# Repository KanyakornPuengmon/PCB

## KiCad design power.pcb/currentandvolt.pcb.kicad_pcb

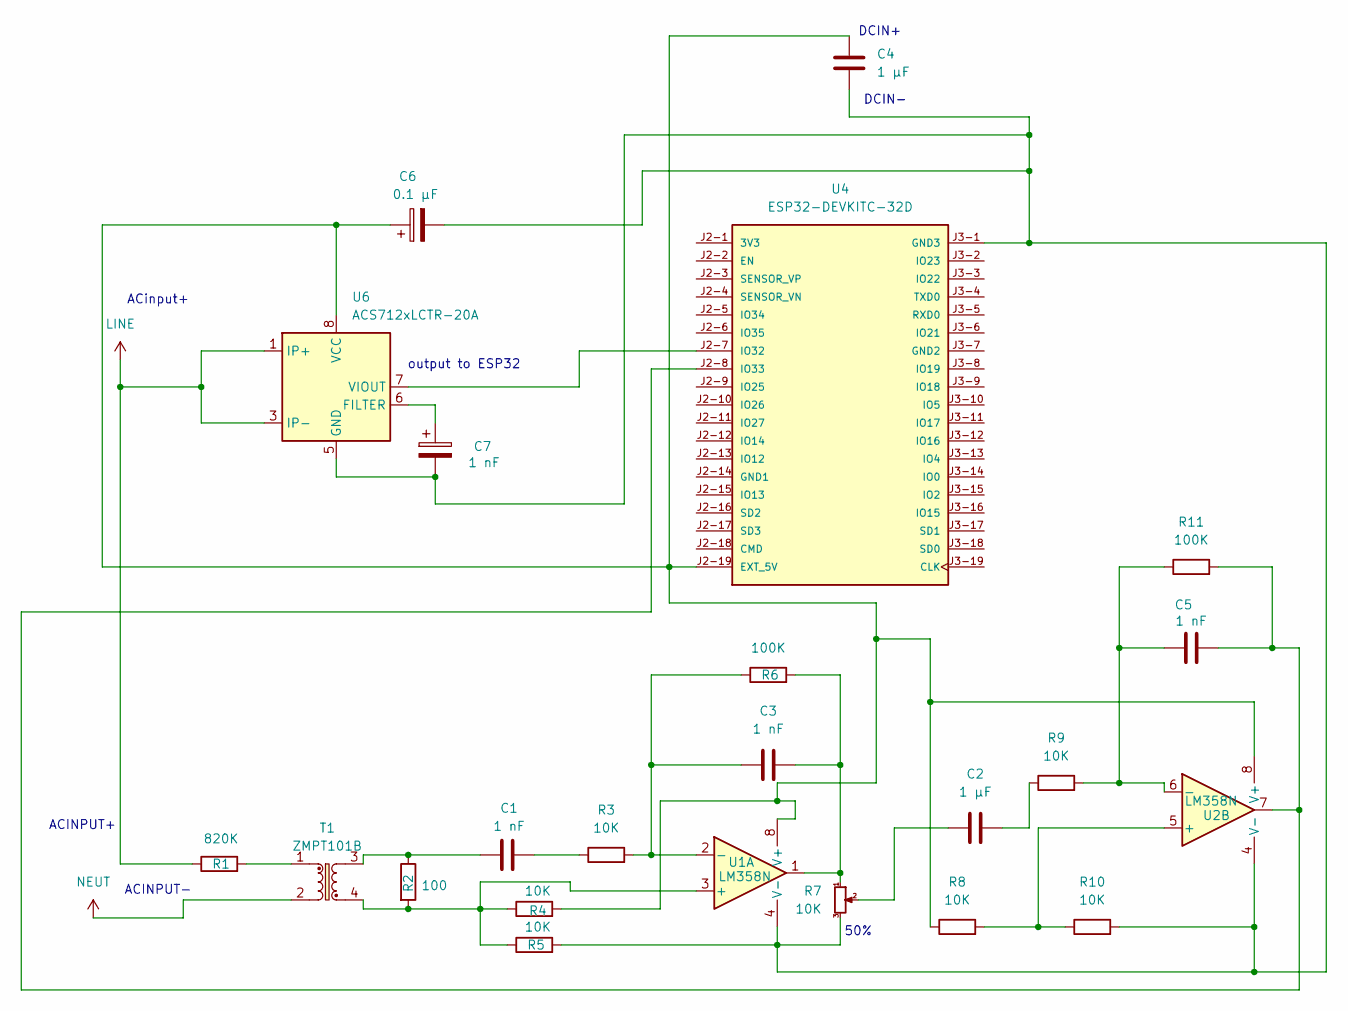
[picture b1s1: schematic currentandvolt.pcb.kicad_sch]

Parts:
C1, C3, C5: 1 nF; CP_Radial_D8.0mm_P3.50mm
C2, C4: 1 µF; CP_Radial_D8.0mm_P3.50mm
C6: 0.1 µF; CP_Radial_D8.0mm_P2.50mm
C7: 1 nF; CP_Radial_D8.0mm_P2.50mm
R1: 820K; R_Axial_DIN0207_L6.3mm_D2.5mm_P10.16mm_Horizontal
R2: 100; R_Axial_DIN0207_L6.3mm_D2.5mm_P10.16mm_Horizontal
R3, R4, R5, R8, R9, R10: 10K; R_Axial_DIN0207_L6.3mm_D2.5mm_P10.16mm_Horizontal
R6, R11: 100K; R_Axial_DIN0207_L6.3mm_D2.5mm_P10.16mm_Horizontal
R7: 10K; Potentiometer_Bourns_3296X_Horizontal
T1: ZMPT101B; Transformer_Zeming_ZMPT101K
U1, U2: LM358N; DIP-8_W7.62mm_LongPads
U3, U5: LM358; DIP-8_W7.62mm_LongPads
U4: ESP32-DEVKITC-32D; MODULE_ESP32-DEVKITC-32D; PARTREV V4
U6: ACS712xLCTR-20A; SOIC-8_3.9x4.9mm_P1.27mm

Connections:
LINE: R1.1, U6.1 (IP+), U6.2 (IP+), U6.3 (IP-), U6.4 (IP-)
NEUT: T1.2
unnamed: C1.1, R2.1, T1.3
unnamed: C1.2, R3.1
unnamed: C2.1, R7.2
unnamed: C2.2, R9.1
unnamed: C3.2, R6.2, R7.1, U1.1
unnamed: R1.2, T1.1
unnamed: R2.2, R4.1, R5.1, T1.4, U1.3 (+)
unnamed: C3.1, R3.2, R6.1, U1.2 (-)
unnamed: R8.2, R10.1, U2.5 (+)
unnamed: C5.1, R9.2, R11.1, U2.6 (-)
unnamed: C4.1, C6.1, R4.2, R8.1, U3.8 (V+), U4.J2-19 (EXT_5V), U5.8 (V+), U6.8 (VCC)
unnamed: C4.2, C6.2, C7.2, R5.2, R7.3, R10.2, U3.4 (V-), U4.J3-1 (GND3), U5.4 (V-), U6.5 (GND)
unnamed: U4.J2-7 (IO32), U6.7 (VIOUT)
unnamed: C5.2, R11.2, U2.7, U4.J2-8 (IO33)
unnamed: C7.1, U6.6 (FILTER)

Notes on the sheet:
ACINPUT+
output to ESP32
ACinput+
ACINPUT-
DCIN-
50%
DCIN+

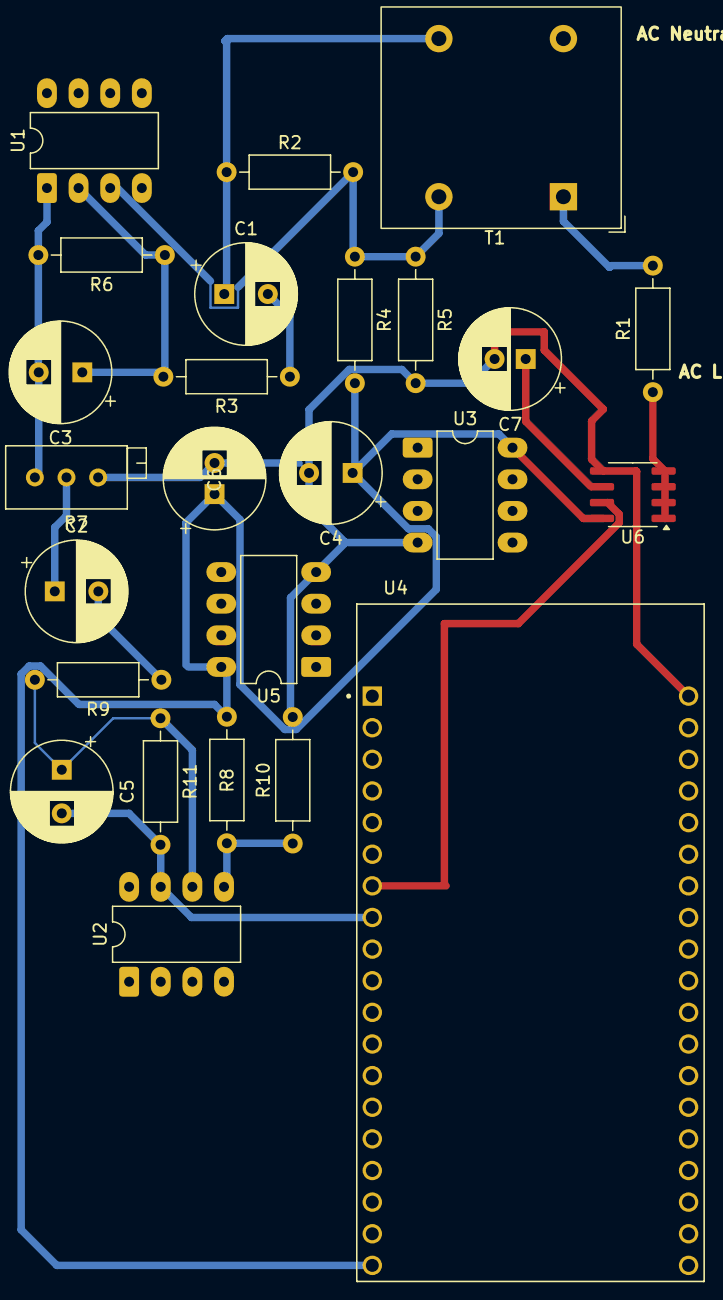
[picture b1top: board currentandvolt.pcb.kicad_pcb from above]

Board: 2 copper layers, 25 parts (0 on the bottom side), 16 nets.
